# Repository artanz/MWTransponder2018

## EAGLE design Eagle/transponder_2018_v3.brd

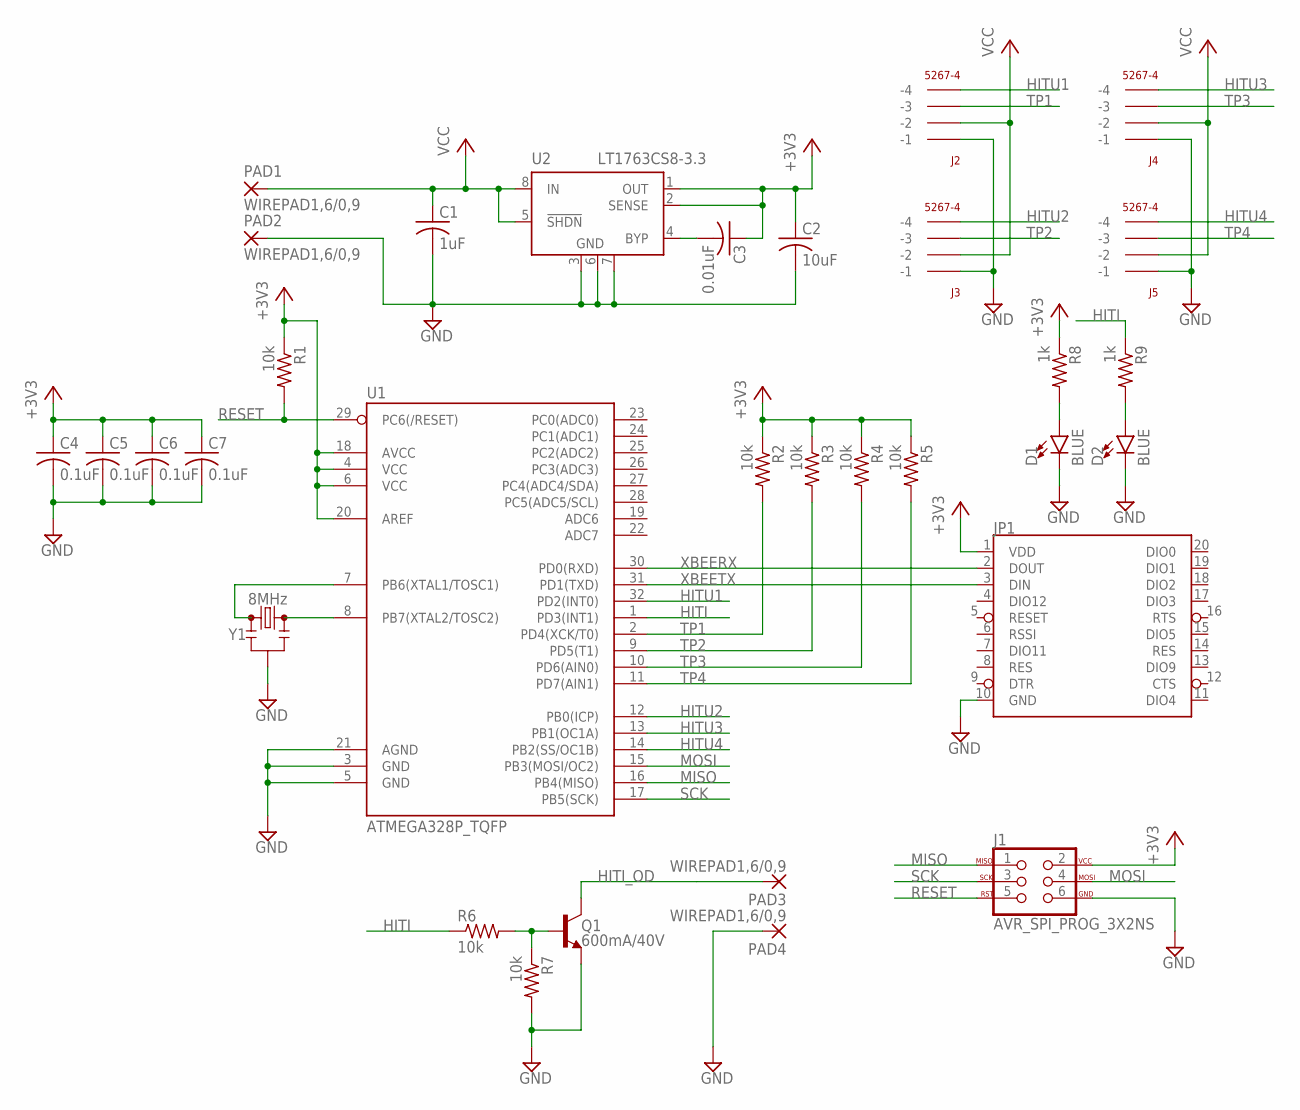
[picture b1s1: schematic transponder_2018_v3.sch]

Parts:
C1: 1uF; C0603
C2: 10uF; C1206
C3: 0.01uF; C0603
C4, C5, C6, C7: 0.1uF; C0603
D1, D2: BLUE; LED-0603
J1: AVR_SPI_PROG_3X2NS; 2X3-NS
J2, J3, J4, J5: 5267-4
JP1: XBEESMD; XBEE-SMD
PAD1, PAD2, PAD3, PAD4: WIREPAD1,6/0,9; 1,6/0,9
Q1: 600mA/40V; SOT23-3
R1, R2, R3, R4, R5, R6, R7: 10k; R0603
R8, R9: 1k; R0603
U1: ATMEGA328P_TQFP; TQFP32-08
U2: LT1763CS8-3.3; SOIC8
Y1: 8MHz; RESONATOR-SMD-3.2X1.3

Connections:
+3V3: C2.1, C3.1, C4.1, C5.1, C6.1, C7.1, J1.2, JP1.1 (VDD), R1.1, R2.1, R3.1, R4.1, R5.1, R8.1, U1.4 (VCC), U1.6 (VCC), U1.18 (AVCC), U1.20 (AREF), U2.1 (OUT), U2.2 (SENSE)
GND: C1.2, C2.2, C4.2, C5.2, C6.2, C7.2, D1.C, D2.C, J1.6, J2.P$1 (-1), J3.P$1 (-1), J4.P$1 (-1), J5.P$1 (-1), JP1.10 (GND), PAD2.1, PAD4.1, Q1.2 (E), R7.2, U1.3 (GND), U1.5 (GND), U1.21 (AGND), U2.3 (GND), U2.6 (GND), U2.7 (GND), Y1.2
HITI: R6.1, R9.1, U1.1 (PD3(INT1))
HITI_OD: PAD3.1, Q1.3 (C)
HITU1: J2.P$4 (-4), U1.32 (PD2(INT0))
HITU2: J3.P$4 (-4), U1.12 (PB0(ICP))
HITU3: J4.P$4 (-4), U1.13 (PB1(OC1A))
HITU4: J5.P$4 (-4), U1.14 (PB2(SS/OC1B))
MISO: J1.1, U1.16 (PB4(MISO))
MOSI: J1.4, U1.15 (PB3(MOSI/OC2))
unnamed: U1.8 (PB7(XTAL2/TOSC2)), Y1.3
unnamed: U1.7 (PB6(XTAL1/TOSC1)), Y1.1
unnamed: D1.A, R8.2
unnamed: Q1.1 (B), R6.2, R7.1
unnamed: D2.A, R9.2
unnamed: C3.2, U2.4 (BYP)
RESET: J1.5, R1.2, U1.29 (PC6(/RESET))
SCK: J1.3, U1.17 (PB5(SCK))
TP1: J2.P$3 (-3), R2.2, U1.2 (PD4(XCK/T0))
TP2: J3.P$3 (-3), R3.2, U1.9 (PD5(T1))
TP3: J4.P$3 (-3), R4.2, U1.10 (PD6(AIN0))
TP4: J5.P$3 (-3), R5.2, U1.11 (PD7(AIN1))
VCC: C1.1, J2.P$2 (-2), J3.P$2 (-2), J4.P$2 (-2), J5.P$2 (-2), PAD1.1, U2.5 (!SHDN), U2.8 (IN)
XBEERX: JP1.2 (DOUT), U1.30 (PD0(RXD))
XBEETX: JP1.3 (DIN), U1.31 (PD1(TXD))

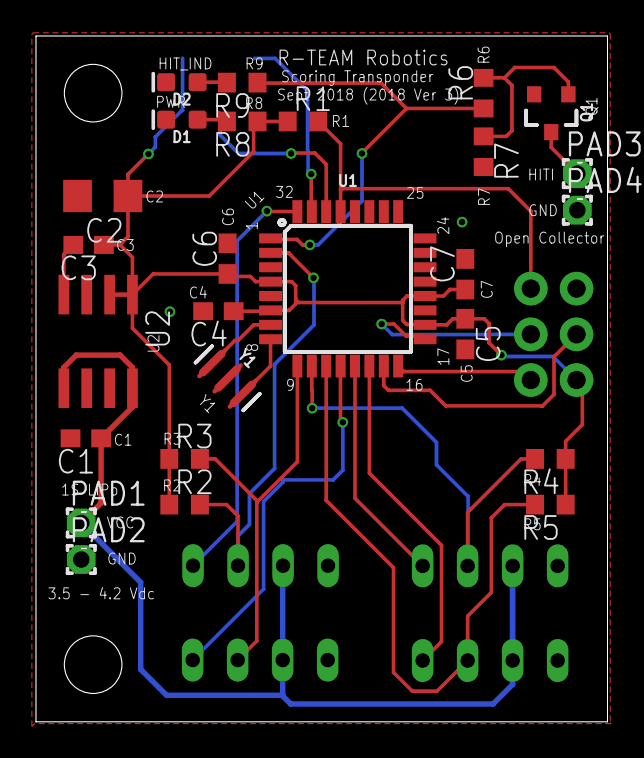
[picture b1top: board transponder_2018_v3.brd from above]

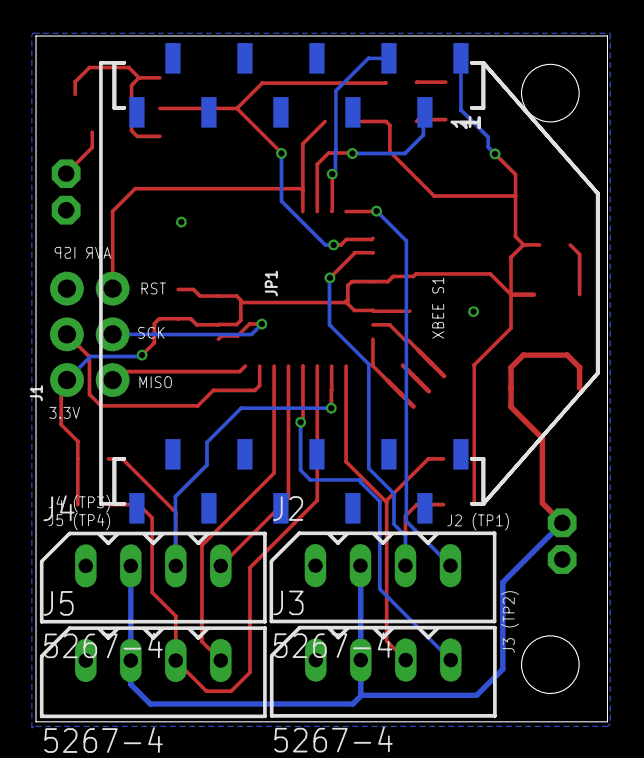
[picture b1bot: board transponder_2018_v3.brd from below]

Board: 2 copper layers, 31.8 x 38.1 mm, 32 parts (6 on the bottom side), 25 nets.

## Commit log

2019-06-02 Add files via upload
    Added V3 Variant, functionally same, slight connector changes

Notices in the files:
parts and their libraries:
SparkFun-Connectors: Licensing: Creative Commons ShareAlike 4.0 International - https://creativecommons.org/licenses/by-sa/4.0
